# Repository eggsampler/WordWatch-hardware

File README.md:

# WordWatch-hardware

|  | Schematic | 2D PCB | 3D |
| --- | --- | --- | --- |
| Controller Board | [ControllerBoard.pdf](ControllerBoard/plots/ControllerBoard.pdf) | [ControllerBoard__Assembly.pdf](ControllerBoard/plots/ControllerBoard__Assembly.pdf) | [ControllerBoard.wrl](ControllerBoard/plots/ControllerBoard.wrl) |
| LED Board | [LEDBoard.pdf](LEDBoard/plots/LEDBoard.pdf) | [LEDBoard__Assembly.pdf](LEDBoard/plots/LEDBoard__Assembly.pdf) | [LEDBoard.wrl](LEDBoard/plots/LEDBoard.wrl) |
| Programming Board | [ProgrammingBoard.pdf](ProgrammingBoard/plots/ProgrammingBoard.pdf) | [ProgrammingBoard__Assembly.pdf](ProgrammingBoard/plots/ProgrammingBoard__Assembly.pdf) | [ProgrammingBoard.wrl](ProgrammingBoard/plots/ProgrammingBoard.wrl) |

PNG outputs for 2D and 3D PCB views also in each plot folder.

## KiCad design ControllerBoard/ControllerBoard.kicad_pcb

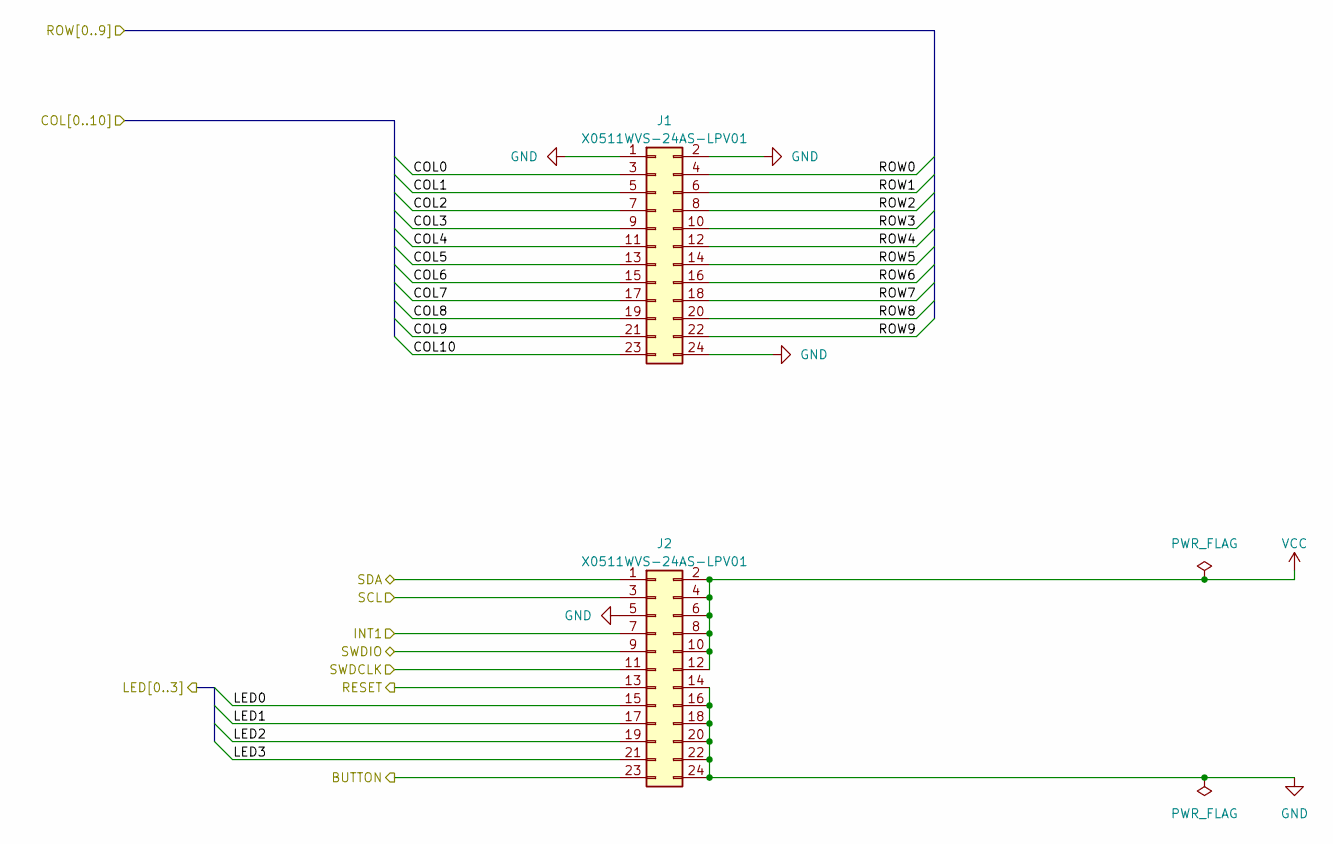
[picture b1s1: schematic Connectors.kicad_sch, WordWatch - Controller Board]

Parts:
J1, J2: X0511WVS-24AS-LPV01

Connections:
/Accelerometer/INT1: J2.7; also elsewhere on the board
/Accelerometer/SCL: J2.3; also elsewhere on the board
/Accelerometer/SDA: J2.1; also elsewhere on the board
/Connectors/BUTTON: J2.23; also elsewhere on the board
/Connectors/COL0: J1.3; also elsewhere on the board
/Connectors/COL1: J1.5; also elsewhere on the board
/Connectors/COL2: J1.7; also elsewhere on the board
/Connectors/COL3: J1.9; also elsewhere on the board
/Connectors/COL4: J1.11; also elsewhere on the board
/Connectors/COL5: J1.13; also elsewhere on the board
/Connectors/COL6: J1.15; also elsewhere on the board
/Connectors/COL7: J1.17; also elsewhere on the board
/Connectors/COL8: J1.19; also elsewhere on the board
/Connectors/COL9: J1.21; also elsewhere on the board
/Connectors/COL10: J1.23; also elsewhere on the board
/Connectors/LED0: J2.15; also elsewhere on the board
/Connectors/LED1: J2.17; also elsewhere on the board
/Connectors/LED2: J2.19; also elsewhere on the board
/Connectors/LED3: J2.21; also elsewhere on the board
/Connectors/ROW0: J1.4; also elsewhere on the board
/Connectors/ROW1: J1.6; also elsewhere on the board
/Connectors/ROW2: J1.8; also elsewhere on the board
/Connectors/ROW3: J1.10; also elsewhere on the board
/Connectors/ROW4: J1.12; also elsewhere on the board
/Connectors/ROW5: J1.14; also elsewhere on the board
/Connectors/ROW6: J1.16; also elsewhere on the board
/Connectors/ROW7: J1.18; also elsewhere on the board
/Connectors/ROW8: J1.20; also elsewhere on the board
/Connectors/ROW9: J1.22; also elsewhere on the board
/Connectors/SWDCLK: J2.11; also elsewhere on the board
/Connectors/SWDIO: J2.9; also elsewhere on the board
/Microcontroller/RESET: J2.13; also elsewhere on the board
GND: J1.1, J1.2, J1.24, J2.5, J2.14, J2.16, J2.18, J2.20, J2.22, J2.24; also elsewhere on the board
VCC: J2.2, J2.4, J2.6, J2.8, J2.10, J2.12; also elsewhere on the board

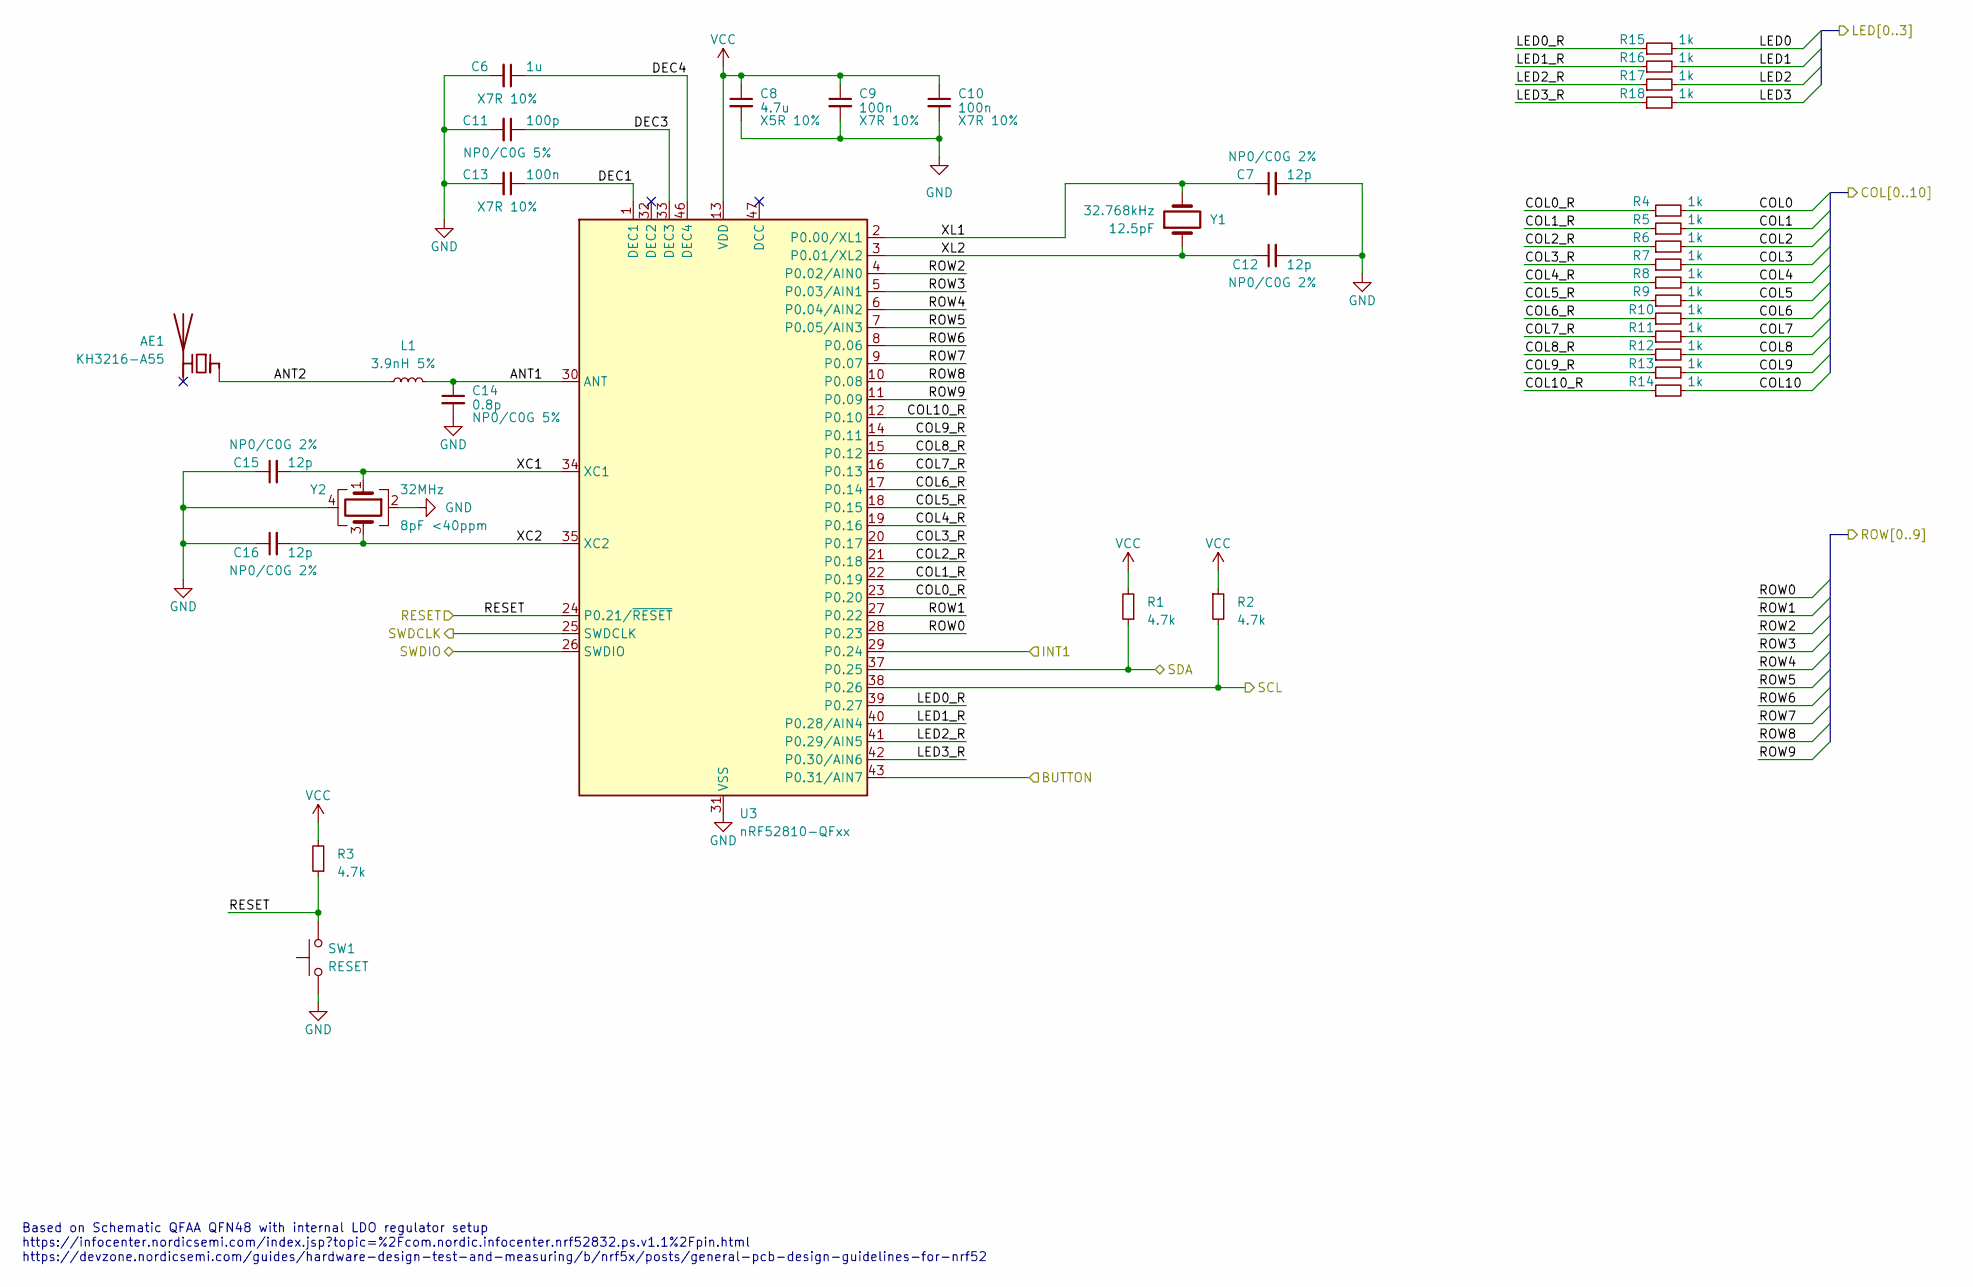
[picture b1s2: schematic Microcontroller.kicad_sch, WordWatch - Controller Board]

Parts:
AE1: KH3216-A55; R_1206_3216Metric
C6: 1u; C_0603_1608Metric
C7, C12, C15, C16: 12p; C_0402_1005Metric
C8: 4.7u; C_0603_1608Metric
C9, C10, C13: 100n; C_0402_1005Metric
C11: 100p; C_0402_1005Metric
C14: 0.8p; C_0402_1005Metric
L1: 3.9nH; L_0402_1005Metric
R1, R2, R3: 4.7k; R_0402_1005Metric
R4, R5, R6, R7, R8, R9, R10, R11, R12, R13, R14, R15, R16, R17, R18: 1k; R_0402_1005Metric
SW1: RESET; SW_Push_SPST_NO_Alps_SKRK
U3: nRF52810-QFxx; QFN-48-1EP_6x6mm_P0.4mm_EP4.6x4.6mm
Y1: 32.768kHz; Crystal_SMD_3215-2Pin_3.2x1.5mm
Y2: 32MHz; Oscillator_SMD_Abracon_ASCO-4Pin_1.6x1.2mm

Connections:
/Accelerometer/INT1: U3.29 (P0.24); also elsewhere on the board
/Accelerometer/SCL: R2.2, U3.38 (P0.26); also elsewhere on the board
/Accelerometer/SDA: R1.1, U3.37 (P0.25); also elsewhere on the board
/Connectors/BUTTON: U3.43 (P0.31/AIN7); also elsewhere on the board
/Connectors/COL0: R4.2; also elsewhere on the board
/Connectors/COL1: R5.2; also elsewhere on the board
/Connectors/COL2: R6.2; also elsewhere on the board
/Connectors/COL3: R7.2; also elsewhere on the board
/Connectors/COL4: R8.2; also elsewhere on the board
/Connectors/COL5: R9.2; also elsewhere on the board
/Connectors/COL6: R10.2; also elsewhere on the board
/Connectors/COL7: R11.2; also elsewhere on the board
/Connectors/COL8: R12.2; also elsewhere on the board
/Connectors/COL9: R13.2; also elsewhere on the board
/Connectors/COL10: R14.2; also elsewhere on the board
/Connectors/LED0: R15.2; also elsewhere on the board
/Connectors/LED1: R16.2; also elsewhere on the board
/Connectors/LED2: R17.2; also elsewhere on the board
/Connectors/LED3: R18.2; also elsewhere on the board
/Connectors/ROW0: U3.28 (P0.23); also elsewhere on the board
/Connectors/ROW1: U3.27 (P0.22); also elsewhere on the board
/Connectors/ROW2: U3.4 (P0.02/AIN0); also elsewhere on the board
/Connectors/ROW3: U3.5 (P0.03/AIN1); also elsewhere on the board
/Connectors/ROW4: U3.6 (P0.04/AIN2); also elsewhere on the board
/Connectors/ROW5: U3.7 (P0.05/AIN3); also elsewhere on the board
/Connectors/ROW6: U3.8 (P0.06); also elsewhere on the board
/Connectors/ROW7: U3.9 (P0.07); also elsewhere on the board
/Connectors/ROW8: U3.10 (P0.08); also elsewhere on the board
/Connectors/ROW9: U3.11 (P0.09); also elsewhere on the board
/Connectors/SWDCLK: U3.25 (SWDCLK); also elsewhere on the board
/Connectors/SWDIO: U3.26 (SWDIO); also elsewhere on the board
/Microcontroller/ANT1: C14.1, L1.2, U3.30 (ANT)
/Microcontroller/ANT2: AE1.1 (FEED), L1.1
/Microcontroller/COL0_R: R4.1, U3.23 (P0.20)
/Microcontroller/COL1_R: R5.1, U3.22 (P0.19)
/Microcontroller/COL2_R: R6.1, U3.21 (P0.18)
/Microcontroller/COL3_R: R7.1, U3.20 (P0.17)
/Microcontroller/COL4_R: R8.1, U3.19 (P0.16)
/Microcontroller/COL5_R: R9.1, U3.18 (P0.15)
/Microcontroller/COL6_R: R10.1, U3.17 (P0.14)
/Microcontroller/COL7_R: R11.1, U3.16 (P0.13)
/Microcontroller/COL8_R: R12.1, U3.15 (P0.12)
/Microcontroller/COL9_R: R13.1, U3.14 (P0.11)
/Microcontroller/COL10_R: R14.1, U3.12 (P0.10)
/Microcontroller/DEC1: C13.1, U3.1 (DEC1)
/Microcontroller/DEC3: C11.1, U3.33 (DEC3)
/Microcontroller/DEC4: C6.1, U3.46 (DEC4)
/Microcontroller/LED0_R: R15.1, U3.39 (P0.27)
/Microcontroller/LED1_R: R16.1, U3.40 (P0.28/AIN4)
/Microcontroller/LED2_R: R17.1, U3.41 (P0.29/AIN5)
/Microcontroller/LED3_R: R18.1, U3.42 (P0.30/AIN6)
/Microcontroller/RESET: R3.1, SW1.2, U3.24 (P0.21/~RESET); also elsewhere on the board
/Microcontroller/XC1: C15.2, U3.34 (XC1), Y2.1
/Microcontroller/XC2: C16.2, U3.35 (XC2), Y2.3
/Microcontroller/XL1: C7.1, U3.2 (P0.00/XL1), Y1.2
/Microcontroller/XL2: C12.1, U3.3 (P0.01/XL2), Y1.1
GND: C6.2, C7.2, C8.2, C9.2, C10.2, C11.2, C12.2, C13.2, C14.2, C15.1, C16.1, SW1.1, U3.31 (VSS), U3.45 (VSS), U3.49 (VSS), Y2.2, Y2.4; also elsewhere on the board
VCC: C8.1, C9.1, C10.1, R1.2, R2.1, R3.2, U3.13 (VDD), U3.36 (VDD), U3.48 (VDD); also elsewhere on the board

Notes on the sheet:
Based on Schematic QFAA QFN48 with internal LDO regulator setup https://infocenter.nordicsemi.com/index.jsp?topic=%2Fcom.nordic.infocenter.nrf52832.ps.v1.1%2Fpin.html https://devzone.nordicsemi.com/guides/hardware-design-test-and-measuring/b/nrf5x/posts/general-pcb-design-guidelines-for-nrf52

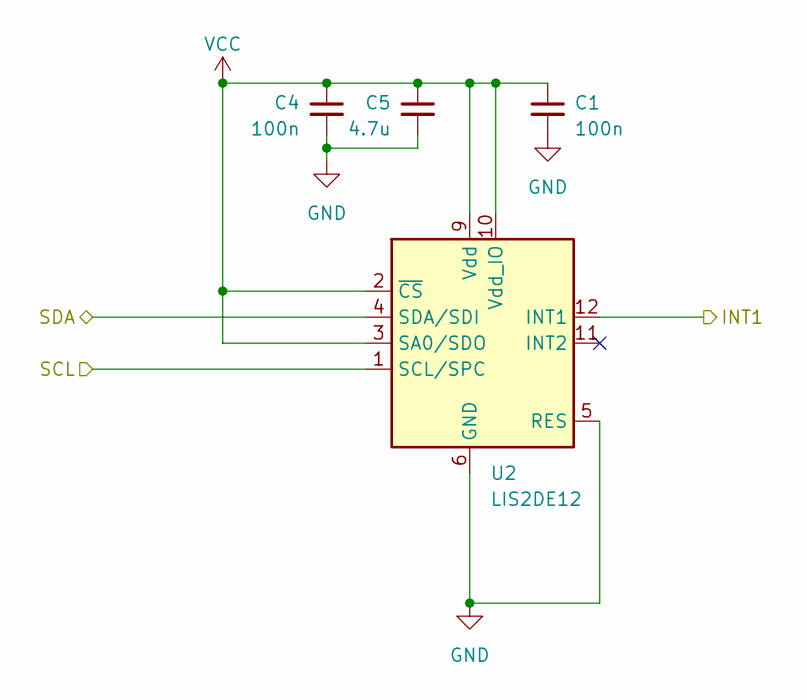
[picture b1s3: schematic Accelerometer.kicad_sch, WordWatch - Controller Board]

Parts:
C1, C4: 100n; C_0402_1005Metric
C5: 4.7u; C_0603_1608Metric
U2: LIS2DE12; LGA-12_2x2mm_P0.5mm

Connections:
/Accelerometer/INT1: U2.12 (INT1); also elsewhere on the board
/Accelerometer/SCL: U2.1 (SCL/SPC); also elsewhere on the board
/Accelerometer/SDA: U2.4 (SDA/SDI); also elsewhere on the board
GND: C1.2, C4.2, C5.2, U2.5 (RES), U2.6 (GND), U2.7 (GND), U2.8 (GND); also elsewhere on the board
VCC: C1.1, C4.1, C5.1, U2.2 (~CS), U2.3 (SA0/SDO), U2.9 (Vdd), U2.10 (Vdd_IO); also elsewhere on the board

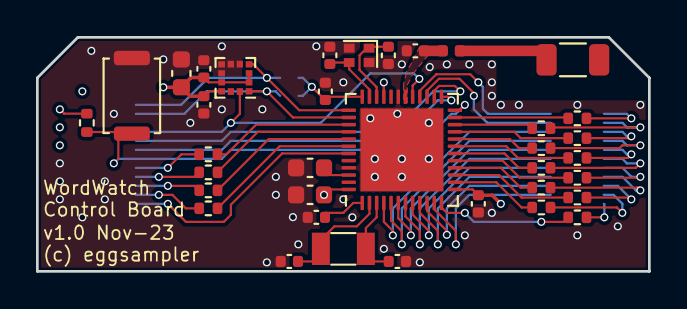
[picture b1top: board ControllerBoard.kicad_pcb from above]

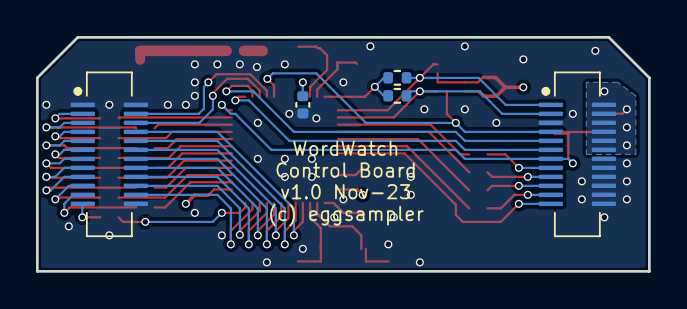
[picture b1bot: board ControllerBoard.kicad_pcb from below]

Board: 4 copper layers, 34.0 x 13.0 mm, 41 parts (5 on the bottom side), 58 nets.

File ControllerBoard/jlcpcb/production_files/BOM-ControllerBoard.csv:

Comment,Designator,Footprint,LCSC
1k,"R10,R11,R12,R13,R14,R15,R16,R17,R18,R4,R5,R6,R7,R8,R9",R_0402_1005Metric,C11702
3.9nH,L1,L_0402_1005Metric,C14033
nRF52810-QFxx,U3,QFN-48-1EP_6x6mm_P0.4mm_EP4.6x4.6mm,C141828
100n,"C1,C10,C13,C4,C9",C_0402_1005Metric,C1525
100p,C11,C_0402_1005Metric,C1546
12p,"C12,C15,C16,C7",C_0402_1005Metric,C1547
LIS2DE12,U2,LGA-12_2x2mm_P0.5mm,C155639
1u,C6,C_0603_1608Metric,C15849
4.7u,"C5,C8",C_0603_1608Metric,C19666
4.7k,"R1,R2,R3",R_0402_1005Metric,C25900
RESET,SW1,SW_Push_SPST_NO_Alps_SKRK,C262416
X0511WVS-24AS-LPV01,"J1,J2",X0511WVS-24AS-LPV01,C2925345
32MHz,Y2,Oscillator_SMD_Abracon_ASCO-4Pin_1.6x1.2mm,C2965582
32.768kHz,Y1,Crystal_SMD_3215-2Pin_3.2x1.5mm,C32346
0.8p,C14,C_0402_1005Metric,C327032
KH3216-A55,AE1,R_1206_3216Metric,C484541

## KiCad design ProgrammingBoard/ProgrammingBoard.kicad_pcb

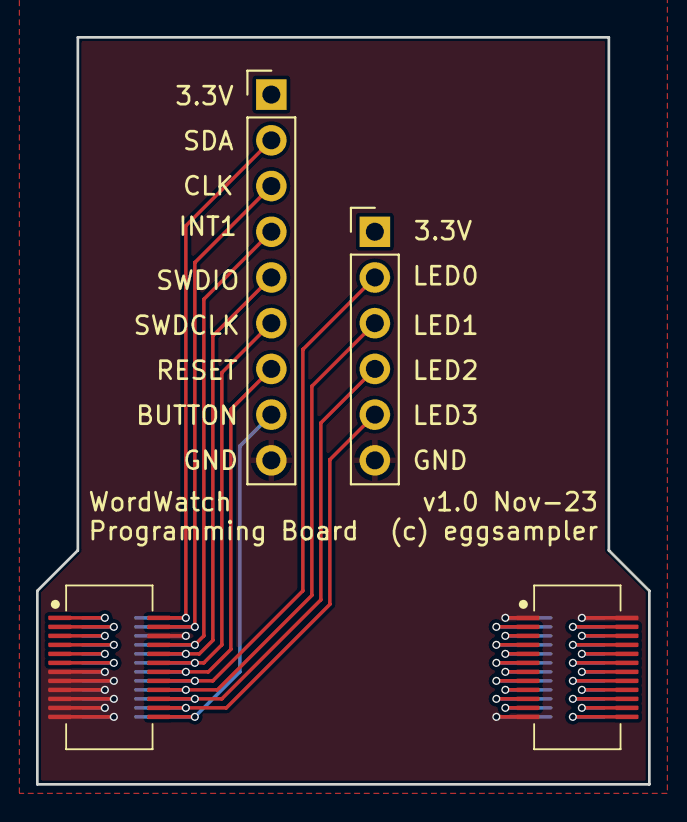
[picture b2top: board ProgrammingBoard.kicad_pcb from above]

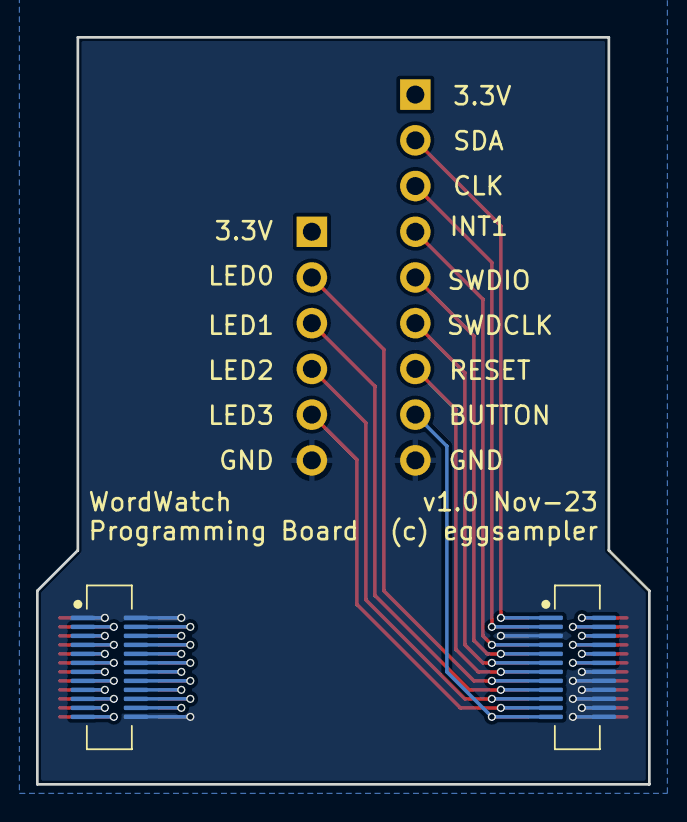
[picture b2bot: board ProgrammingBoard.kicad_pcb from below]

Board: 4 copper layers, 34.0 x 41.5 mm, 6 parts (2 on the bottom side), 34 nets.

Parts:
J1, J3: X0511WVS-24AS-LPV01
J2, J4: X0511FVS-24AS-LPV01
J5: Conn_01x06; PinHeader_1x06_P2.54mm_Vertical
J6: Conn_01x09; PinHeader_1x09_P2.54mm_Vertical

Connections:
/Connectors/BUTTON: J3.23, J4.24, J6.8
/Connectors/COL0: J1.3, J2.4
/Connectors/COL1: J1.5, J2.6
/Connectors/COL2: J1.7, J2.8
/Connectors/COL3: J1.9, J2.10
/Connectors/COL4: J1.11, J2.12
/Connectors/COL5: J1.13, J2.14
/Connectors/COL6: J1.15, J2.16
/Connectors/COL7: J1.17, J2.18
/Connectors/COL8: J1.19, J2.20
/Connectors/COL9: J1.21, J2.22
/Connectors/COL10: J1.23, J2.24
/Connectors/INT1: J3.7, J4.8, J6.4
/Connectors/LED0: J3.15, J4.16, J5.2
/Connectors/LED1: J3.17, J4.18, J5.3
/Connectors/LED2: J3.19, J4.20, J5.4
/Connectors/LED3: J3.21, J4.22, J5.5
/Connectors/RESET: J3.13, J4.14, J6.7
/Connectors/ROW0: J1.4, J2.3
/Connectors/ROW1: J1.6, J2.5
/Connectors/ROW2: J1.8, J2.7
/Connectors/ROW3: J1.10, J2.9
/Connectors/ROW4: J1.12, J2.11
/Connectors/ROW5: J1.14, J2.13
/Connectors/ROW6: J1.16, J2.15
/Connectors/ROW7: J1.18, J2.17
/Connectors/ROW8: J1.20, J2.19
/Connectors/ROW9: J1.22, J2.21
/Connectors/SCL: J3.3, J4.4, J6.3
/Connectors/SDA: J3.1, J4.2, J6.2
/Connectors/SWDCLK: J3.11, J4.12, J6.6
/Connectors/SWDIO: J3.9, J4.10, J6.5
GND: J1.1, J1.2, J1.24, J2.1, J2.2, J2.23, J3.5, J3.14, J3.16, J3.18, J3.20, J3.22, J3.24, J4.6, J4.13, J4.15, J4.17, J4.19, J4.21, J4.23, J5.6, J6.9
VCC: J3.2, J3.4, J3.6, J3.8, J3.10, J3.12, J4.1, J4.3, J4.5, J4.7, J4.9, J4.11, J5.1, J6.1

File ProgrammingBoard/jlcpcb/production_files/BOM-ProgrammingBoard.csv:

Comment,Designator,Footprint,LCSC
X0511WVS-24AS-LPV01,"J1,J3",X0511WVS-24AS-LPV01,C2925345
X0511FVS-24AS-LPV01,"J2,J4",X0511FVS-24AS-LPV01,C2925346
Conn_01x09,J6,PinHeader_1x09_P2.54mm_Vertical,
Conn_01x06,J5,PinHeader_1x06_P2.54mm_Vertical,

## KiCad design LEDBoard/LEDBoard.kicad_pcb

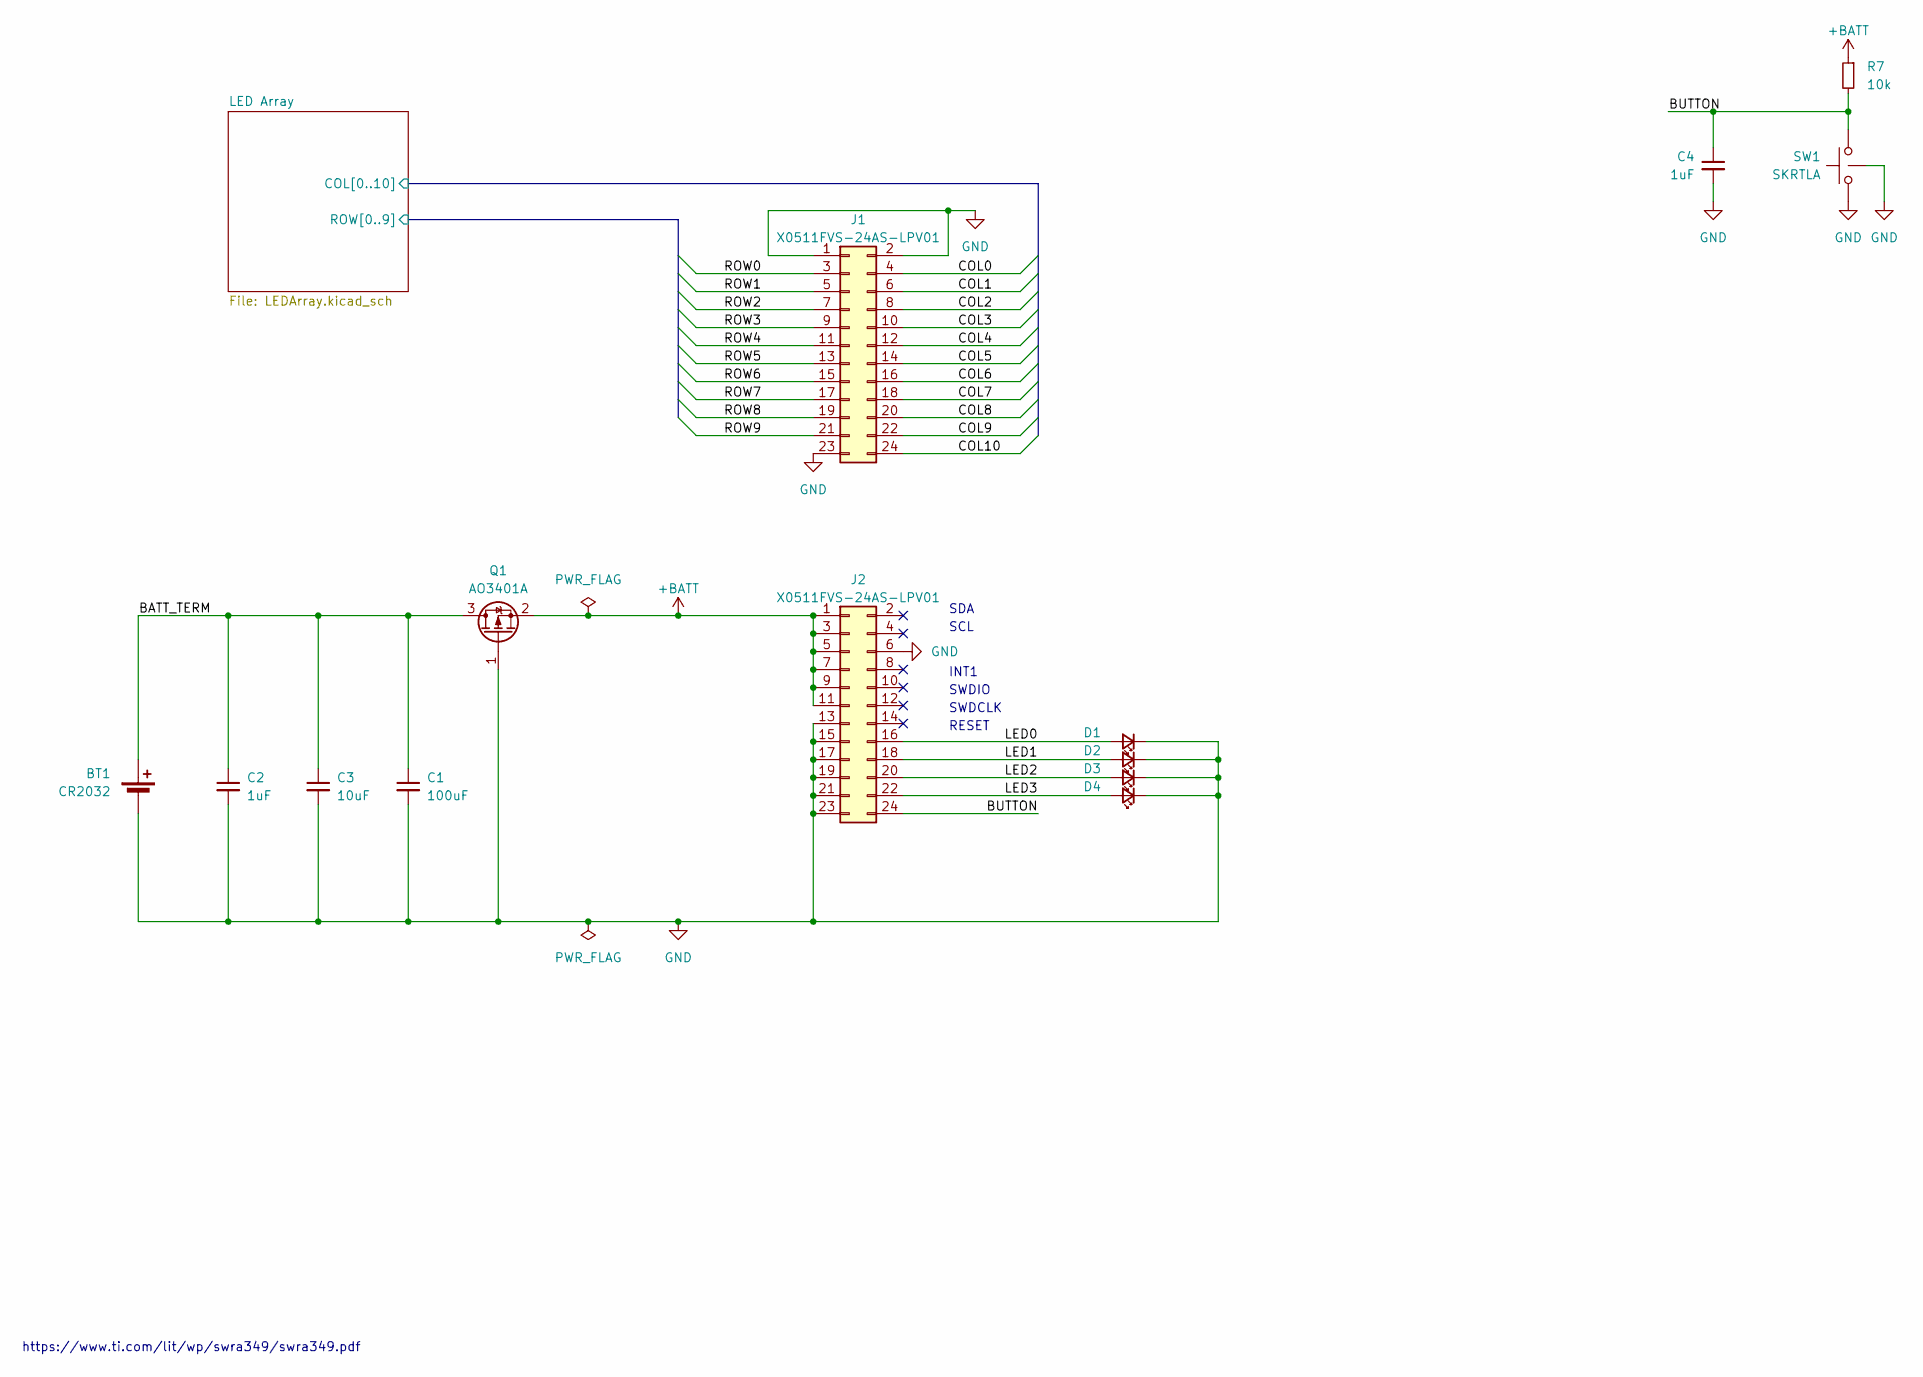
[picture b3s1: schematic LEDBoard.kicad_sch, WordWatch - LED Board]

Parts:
BT1: CR2032; BatteryHolder_Keystone_1060_1x2032
C1: 100uF; C_1206_3216Metric
C2, C4: 1uF; C_0402_1005Metric
C3: 10uF; C_0603_1608Metric
D1, D2, D3, D4: LED_Small; LED_0402_1005Metric
J1, J2: X0511FVS-24AS-LPV01
Q1: AO3401A; SOT-23
R7: 10k; R_0402_1005Metric
SW1: SKRTLA; SW_Push_1P1T-MP_NO_Horizontal_Alps_SKRTLAE010

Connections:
+BATT: J2.1, J2.3, J2.5, J2.7, J2.9, J2.11, Q1.2 (S), R7.1; also elsewhere on the board
/BATT_TERM: BT1.1 (+), C1.1, C2.1, C3.1, Q1.3 (D)
/BUTTON: C4.1, J2.24, R7.2, SW1.2
/LED0: D1.2 (A), J2.16
/LED1: D2.2 (A), J2.18
/LED2: D3.2 (A), J2.20
/LED3: D4.2 (A), J2.22
/LED Array/COL0: J1.4; also elsewhere on the board
/LED Array/COL1: J1.6; also elsewhere on the board
/LED Array/COL2: J1.8; also elsewhere on the board
/LED Array/COL3: J1.10; also elsewhere on the board
/LED Array/COL4: J1.12; also elsewhere on the board
/LED Array/COL5: J1.14; also elsewhere on the board
/LED Array/COL6: J1.16; also elsewhere on the board
/LED Array/COL7: J1.18; also elsewhere on the board
/LED Array/COL8: J1.20; also elsewhere on the board
/LED Array/COL9: J1.22; also elsewhere on the board
/LED Array/COL10: J1.24; also elsewhere on the board
/LED Array/ROW0: J1.3; also elsewhere on the board
/LED Array/ROW1: J1.5; also elsewhere on the board
/LED Array/ROW2: J1.7; also elsewhere on the board
/LED Array/ROW3: J1.9; also elsewhere on the board
/LED Array/ROW4: J1.11; also elsewhere on the board
/LED Array/ROW5: J1.13; also elsewhere on the board
/LED Array/ROW6: J1.15; also elsewhere on the board
/LED Array/ROW7: J1.17; also elsewhere on the board
/LED Array/ROW8: J1.19; also elsewhere on the board
/LED Array/ROW9: J1.21; also elsewhere on the board
GND: BT1.2 (-), C1.2, C2.2, C3.2, C4.2, D1.1 (K), D2.1 (K), D3.1 (K), D4.1 (K), J1.1, J1.2, J1.23, J2.6, J2.13, J2.15, J2.17, J2.19, J2.21, J2.23, Q1.1 (G), SW1.1, SW1.MP; also elsewhere on the board

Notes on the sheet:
SDA
SCL
SWDCLK
INT1
SWDIO
https://www.ti.com/lit/wp/swra349/swra349.pdf
RESET

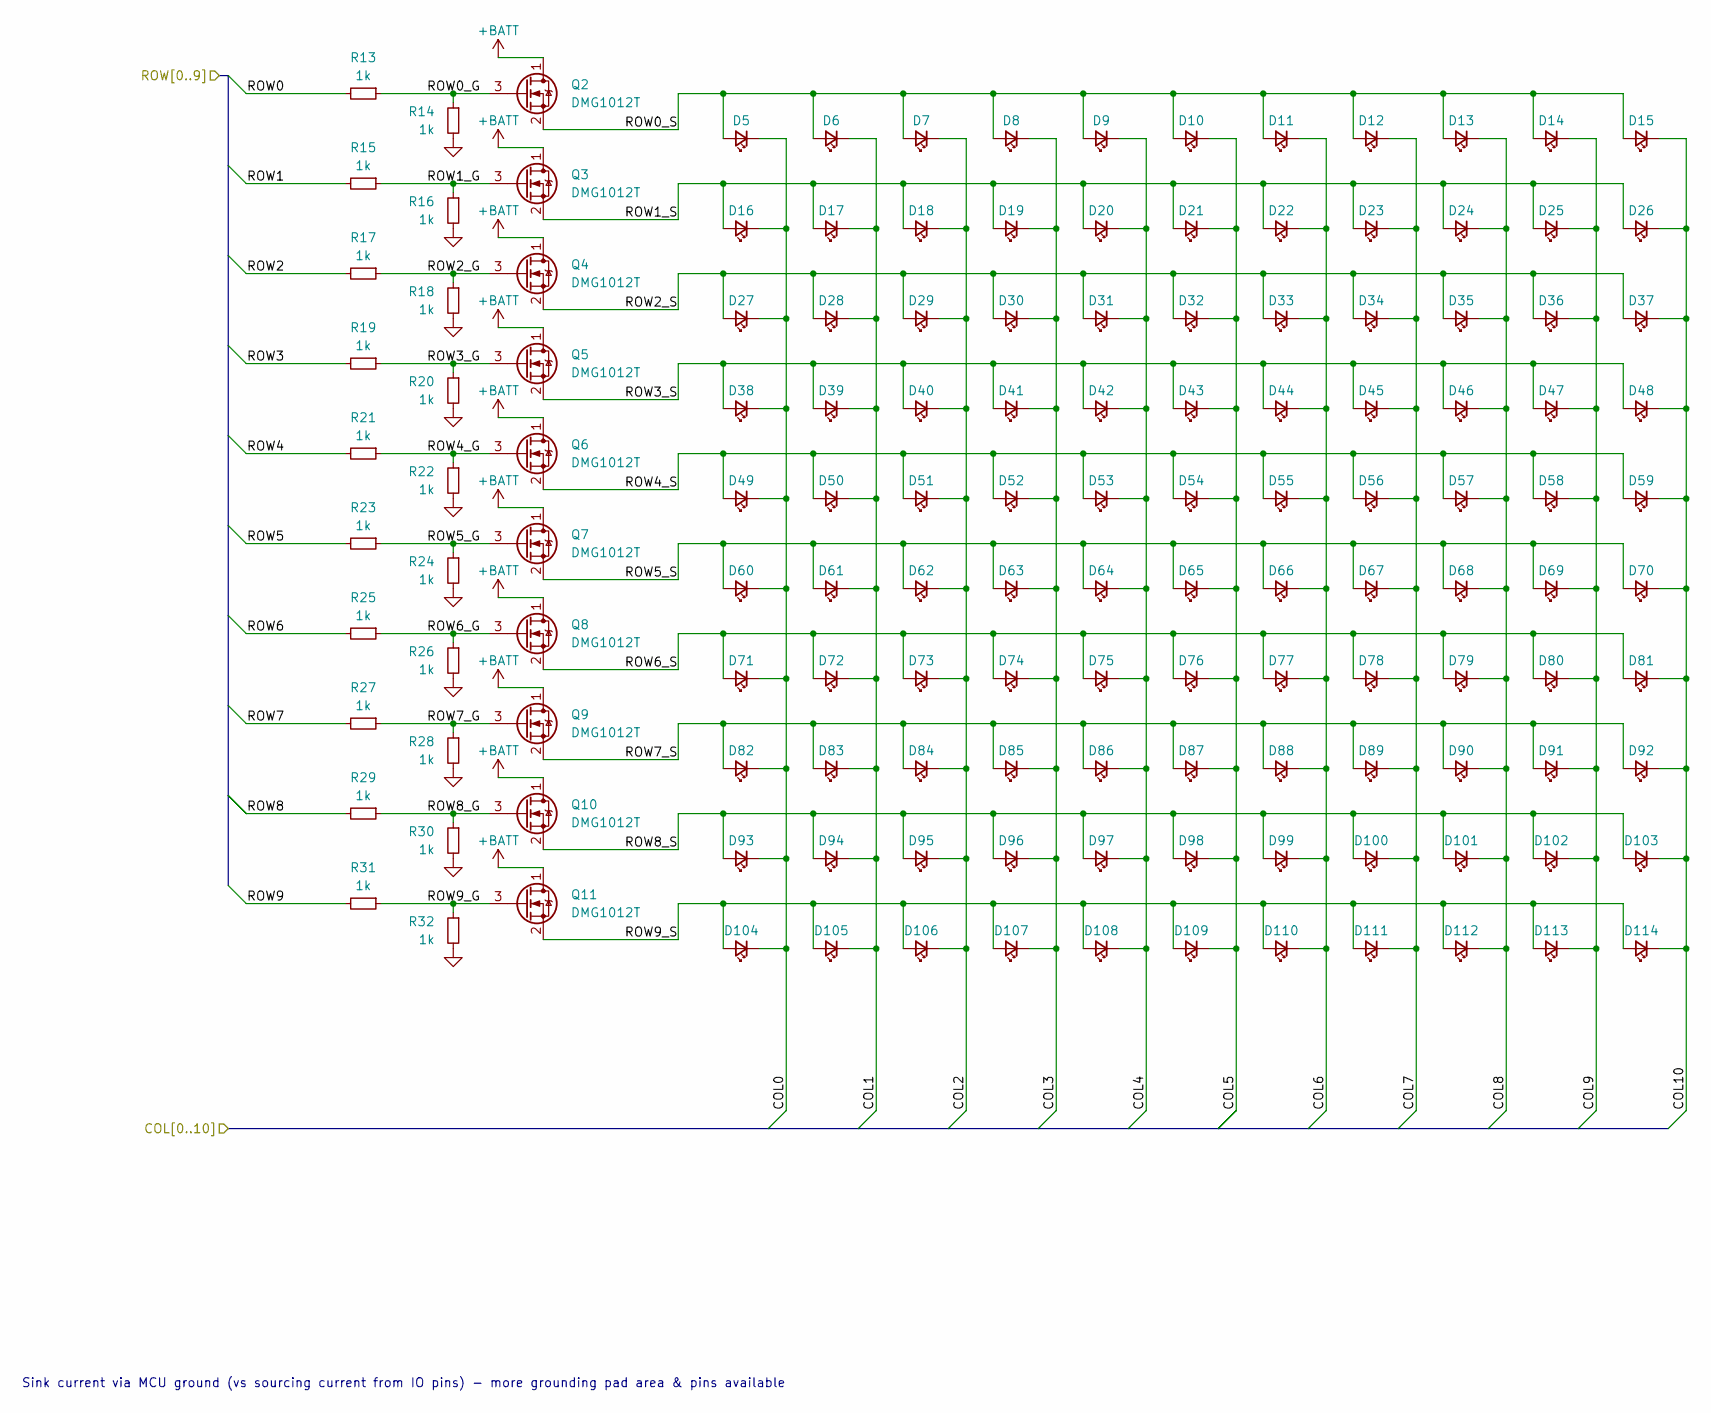
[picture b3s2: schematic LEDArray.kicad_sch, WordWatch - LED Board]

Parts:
D5, D6, D7, D8, D9, D10, D11, D12, D13, D14, D15, D16, D17, D18, D19, D20, D21, D22, D23, D24, D25, D26, D27, D28, D29, D30, D31, D32, D33, D34, D35, D36, D37, D38, D39, D40, D41, D42, D43, D44, D45, D46, D47, D48, D49, D50, D51, D52, D53, D54, D55, D56, D57, D58, D59, D60, D61, D62, D63, D64, D65, D66, D67, D68, D69, D70, D71, D72, D73, D74, D75, D76, D77, D78, D79, D80, D81, D82, D83, D84, D85, D86, D87, D88, D89, D90, D91, D92, D93, D94, D95, D96, D97, D98, D99, D100, D101, D102, D103, D104, D105, D106, D107, D108, D109, D110, D111, D112, D113, D114: LED_Small; LED_0402_1005Metric
Q2, Q3, Q4, Q5, Q6, Q7, Q8, Q9, Q10, Q11: DMG1012T; SOT-523
R13, R14, R15, R16, R17, R18, R19, R20, R21, R22, R23, R24, R25, R26, R27, R28, R29, R30, R31, R32: 1k; R_0402_1005Metric

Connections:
+BATT: Q2.1 (D), Q3.1 (D), Q4.1 (D), Q5.1 (D), Q6.1 (D), Q7.1 (D), Q8.1 (D), Q9.1 (D), Q10.1 (D), Q11.1 (D); also elsewhere on the board
/LED Array/COL0: D5.1 (K), D16.1 (K), D27.1 (K), D38.1 (K), D49.1 (K), D60.1 (K), D71.1 (K), D82.1 (K), D93.1 (K), D104.1 (K); also elsewhere on the board
/LED Array/COL1: D6.1 (K), D17.1 (K), D28.1 (K), D39.1 (K), D50.1 (K), D61.1 (K), D72.1 (K), D83.1 (K), D94.1 (K), D105.1 (K); also elsewhere on the board
/LED Array/COL2: D7.1 (K), D18.1 (K), D29.1 (K), D40.1 (K), D51.1 (K), D62.1 (K), D73.1 (K), D84.1 (K), D95.1 (K), D106.1 (K); also elsewhere on the board
/LED Array/COL3: D8.1 (K), D19.1 (K), D30.1 (K), D41.1 (K), D52.1 (K), D63.1 (K), D74.1 (K), D85.1 (K), D96.1 (K), D107.1 (K); also elsewhere on the board
/LED Array/COL4: D9.1 (K), D20.1 (K), D31.1 (K), D42.1 (K), D53.1 (K), D64.1 (K), D75.1 (K), D86.1 (K), D97.1 (K), D108.1 (K); also elsewhere on the board
/LED Array/COL5: D10.1 (K), D21.1 (K), D32.1 (K), D43.1 (K), D54.1 (K), D65.1 (K), D76.1 (K), D87.1 (K), D98.1 (K), D109.1 (K); also elsewhere on the board
/LED Array/COL6: D11.1 (K), D22.1 (K), D33.1 (K), D44.1 (K), D55.1 (K), D66.1 (K), D77.1 (K), D88.1 (K), D99.1 (K), D110.1 (K); also elsewhere on the board
/LED Array/COL7: D12.1 (K), D23.1 (K), D34.1 (K), D45.1 (K), D56.1 (K), D67.1 (K), D78.1 (K), D89.1 (K), D100.1 (K), D111.1 (K); also elsewhere on the board
/LED Array/COL8: D13.1 (K), D24.1 (K), D35.1 (K), D46.1 (K), D57.1 (K), D68.1 (K), D79.1 (K), D90.1 (K), D101.1 (K), D112.1 (K); also elsewhere on the board
/LED Array/COL9: D14.1 (K), D25.1 (K), D36.1 (K), D47.1 (K), D58.1 (K), D69.1 (K), D80.1 (K), D91.1 (K), D102.1 (K), D113.1 (K); also elsewhere on the board
/LED Array/COL10: D15.1 (K), D26.1 (K), D37.1 (K), D48.1 (K), D59.1 (K), D70.1 (K), D81.1 (K), D92.1 (K), D103.1 (K), D114.1 (K); also elsewhere on the board
/LED Array/ROW0: R13.2; also elsewhere on the board
/LED Array/ROW0_G: Q2.3 (G), R13.1, R14.1
/LED Array/ROW0_S: D5.2 (A), D6.2 (A), D7.2 (A), D8.2 (A), D9.2 (A), D10.2 (A), D11.2 (A), D12.2 (A), D13.2 (A), D14.2 (A), D15.2 (A), Q2.2 (S)
/LED Array/ROW1: R15.2; also elsewhere on the board
/LED Array/ROW1_G: Q3.3 (G), R15.1, R16.1
/LED Array/ROW1_S: D16.2 (A), D17.2 (A), D18.2 (A), D19.2 (A), D20.2 (A), D21.2 (A), D22.2 (A), D23.2 (A), D24.2 (A), D25.2 (A), D26.2 (A), Q3.2 (S)
/LED Array/ROW2: R17.2; also elsewhere on the board
/LED Array/ROW2_G: Q4.3 (G), R17.1, R18.1
/LED Array/ROW2_S: D27.2 (A), D28.2 (A), D29.2 (A), D30.2 (A), D31.2 (A), D32.2 (A), D33.2 (A), D34.2 (A), D35.2 (A), D36.2 (A), D37.2 (A), Q4.2 (S)
/LED Array/ROW3: R19.2; also elsewhere on the board
/LED Array/ROW3_G: Q5.3 (G), R19.1, R20.1
/LED Array/ROW3_S: D38.2 (A), D39.2 (A), D40.2 (A), D41.2 (A), D42.2 (A), D43.2 (A), D44.2 (A), D45.2 (A), D46.2 (A), D47.2 (A), D48.2 (A), Q5.2 (S)
/LED Array/ROW4: R21.2; also elsewhere on the board
/LED Array/ROW4_G: Q6.3 (G), R21.1, R22.1
/LED Array/ROW4_S: D49.2 (A), D50.2 (A), D51.2 (A), D52.2 (A), D53.2 (A), D54.2 (A), D55.2 (A), D56.2 (A), D57.2 (A), D58.2 (A), D59.2 (A), Q6.2 (S)
/LED Array/ROW5: R23.2; also elsewhere on the board
/LED Array/ROW5_G: Q7.3 (G), R23.1, R24.1
/LED Array/ROW5_S: D60.2 (A), D61.2 (A), D62.2 (A), D63.2 (A), D64.2 (A), D65.2 (A), D66.2 (A), D67.2 (A), D68.2 (A), D69.2 (A), D70.2 (A), Q7.2 (S)
/LED Array/ROW6: R25.2; also elsewhere on the board
/LED Array/ROW6_G: Q8.3 (G), R25.1, R26.1
/LED Array/ROW6_S: D71.2 (A), D72.2 (A), D73.2 (A), D74.2 (A), D75.2 (A), D76.2 (A), D77.2 (A), D78.2 (A), D79.2 (A), D80.2 (A), D81.2 (A), Q8.2 (S)
/LED Array/ROW7: R27.2; also elsewhere on the board
/LED Array/ROW7_G: Q9.3 (G), R27.1, R28.1
/LED Array/ROW7_S: D82.2 (A), D83.2 (A), D84.2 (A), D85.2 (A), D86.2 (A), D87.2 (A), D88.2 (A), D89.2 (A), D90.2 (A), D91.2 (A), D92.2 (A), Q9.2 (S)
/LED Array/ROW8: R29.2; also elsewhere on the board
/LED Array/ROW8_G: Q10.3 (G), R29.1, R30.1
/LED Array/ROW8_S: D93.2 (A), D94.2 (A), D95.2 (A), D96.2 (A), D97.2 (A), D98.2 (A), D99.2 (A), D100.2 (A), D101.2 (A), D102.2 (A), D103.2 (A), Q10.2 (S)
/LED Array/ROW9: R31.2; also elsewhere on the board
/LED Array/ROW9_G: Q11.3 (G), R31.1, R32.1
/LED Array/ROW9_S: D104.2 (A), D105.2 (A), D106.2 (A), D107.2 (A), D108.2 (A), D109.2 (A), D110.2 (A), D111.2 (A), D112.2 (A), D113.2 (A), D114.2 (A), Q11.2 (S)
GND: R14.2, R16.2, R18.2, R20.2, R22.2, R24.2, R26.2, R28.2, R30.2, R32.2; also elsewhere on the board

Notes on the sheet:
Sink current via MCU ground (vs sourcing current from IO pins) - more grounding pad area & pins available
